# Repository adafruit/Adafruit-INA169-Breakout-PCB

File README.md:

# Adafruit INA169 Breakout PCB
<a href="http://www.adafruit.com/products/1164"><br/>
Click here to purchase one from the Adafruit shop</a>

This breakout board will solve all your current-monitoring problems. Instead of struggling with a multimeter, you can just use the handy INA169 chip on this breakout to both measure both the DC current draw and have a handy analog output that is with respect to ground. The analog output makes this an ideal breakout for feedback-loop control.

Most current-measuring devices such as our current panel meter are only good for low side measuring. That means that unless you want to get a battery involved, you have to stick the measurement resistor between the target ground and true ground. This can cause problems with circuits since electronics tend to not like it when the ground references change and move with varying current draw. This chip is much smarter - it can handle high side current measuring, up to +60VDC!

PCB files for Adafruit INA169 Analog DC power measurement Breakout. The format is EagleCAD schematic and board layout
- https://www.adafruit.com/product/1164

### License

Adafruit invests time and resources providing this open source design, please support Adafruit and open-source hardware by purchasing products from [Adafruit](https://www.adafruit.com)!

All text above must be included in any redistribution

Designed by Limor Fried/Ladyada for Adafruit Industries.
Creative Commons Attribution/Share-Alike, all text above must be included in any redistribution. 
See license.txt for additional information.

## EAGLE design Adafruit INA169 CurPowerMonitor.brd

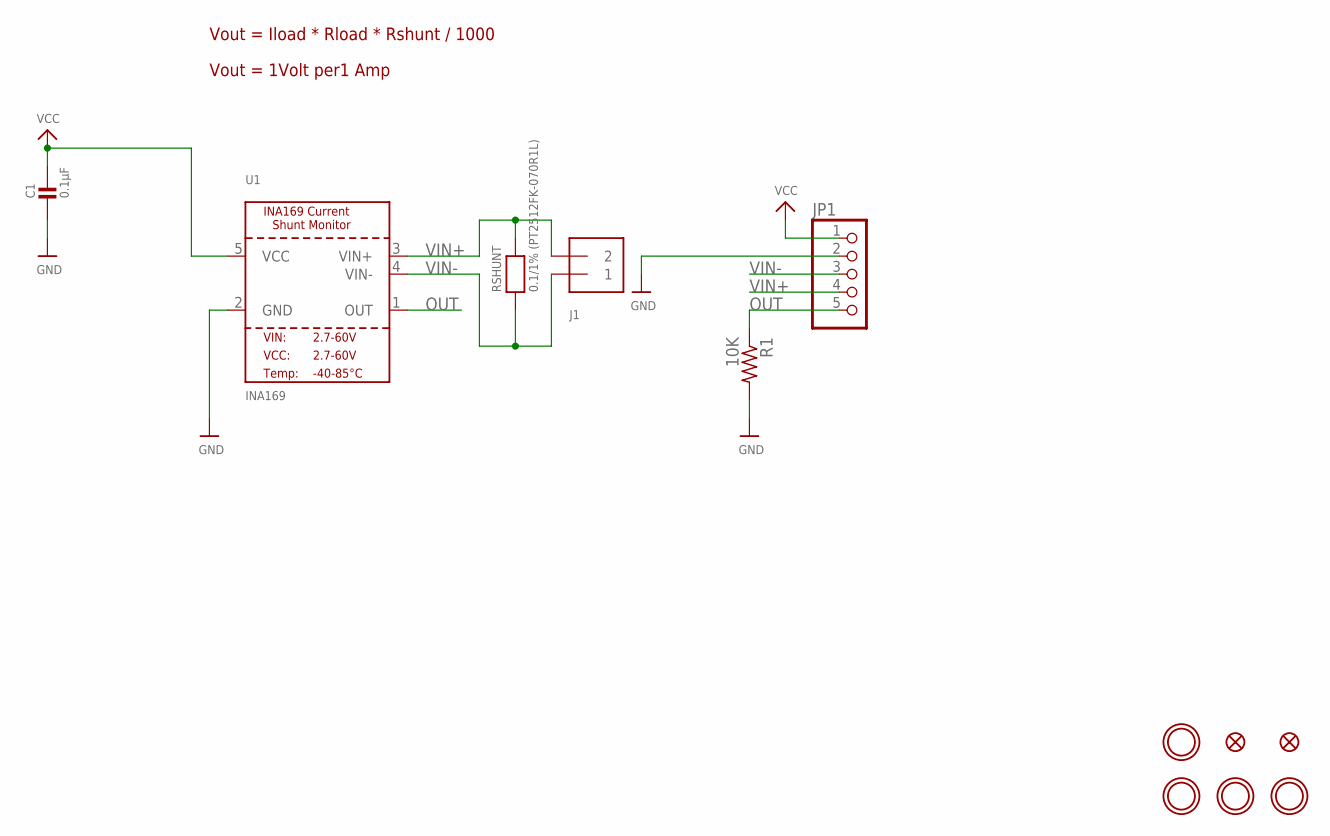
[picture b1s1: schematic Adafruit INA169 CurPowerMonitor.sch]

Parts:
C1: 0.1µF; 0805
FID1, FID2: FIDUCIAL""; FIDUCIAL_1MM
J1: TERMBLOCK_1X2; TERMBLOCK_1X2-3.5MM
JP1: HEADER-1X570MIL; 1X05_ROUND_70
R1: 10K; 0805-THM
RSHUNT: 0.1/1% (PT2512FK-070R1L); 2512
U1: INA169; SOT23-5
U$7, U$8, U$9, U$10: MOUNTINGHOLE2.5; MOUNTINGHOLE_2.5_PLATED

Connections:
GND: C1.2, JP1.2, R1.2, U1.2 (GND)
OUT: JP1.5, R1.1, U1.1 (OUT)
VCC: C1.1, JP1.1, U1.5 (VCC)
VIN+: J1.2, JP1.4, RSHUNT.2, U1.3 (VIN+)
VIN-: J1.1, JP1.3, RSHUNT.1, U1.4 (VIN-)

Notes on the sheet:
Vout = Iload * Rload * Rshunt / 1000
Vout = 1Volt per1 Amp

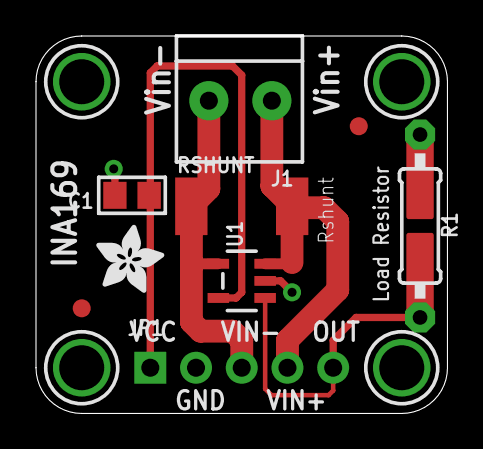
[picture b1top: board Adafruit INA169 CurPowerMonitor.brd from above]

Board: 2 copper layers, 22.9 x 21.0 mm, 13 parts (0 on the bottom side), 5 nets.

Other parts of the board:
U$11: ADAFRUIT_3.5MM

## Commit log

2015-07-21 init
